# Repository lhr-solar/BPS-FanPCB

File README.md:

# BPS Fan PCB

## Purpose
This board is meant to be a passthrough to control fans from the [BPS Leader Board](https://github.com/lhr-solar/BPS-LeaderPCB). Since it is just digital control, it can also be used to control other digital peripherals, such as contactors, however, it cannot read digital inputs. The traces are sized for 1.5A at 25C increase in temperature.

## Connectors
* One 6 Pin Connector (+12V, GND, 4 Fan Control Pins)
* Twelve 2 Pin Connector (+12V, GND)

## Lights
* One LED that turns on when Power is connected to board

## BOM
https://www.mouser.com/ProjectManager/ProjectDetail.aspx?AccessID=d15e40a820

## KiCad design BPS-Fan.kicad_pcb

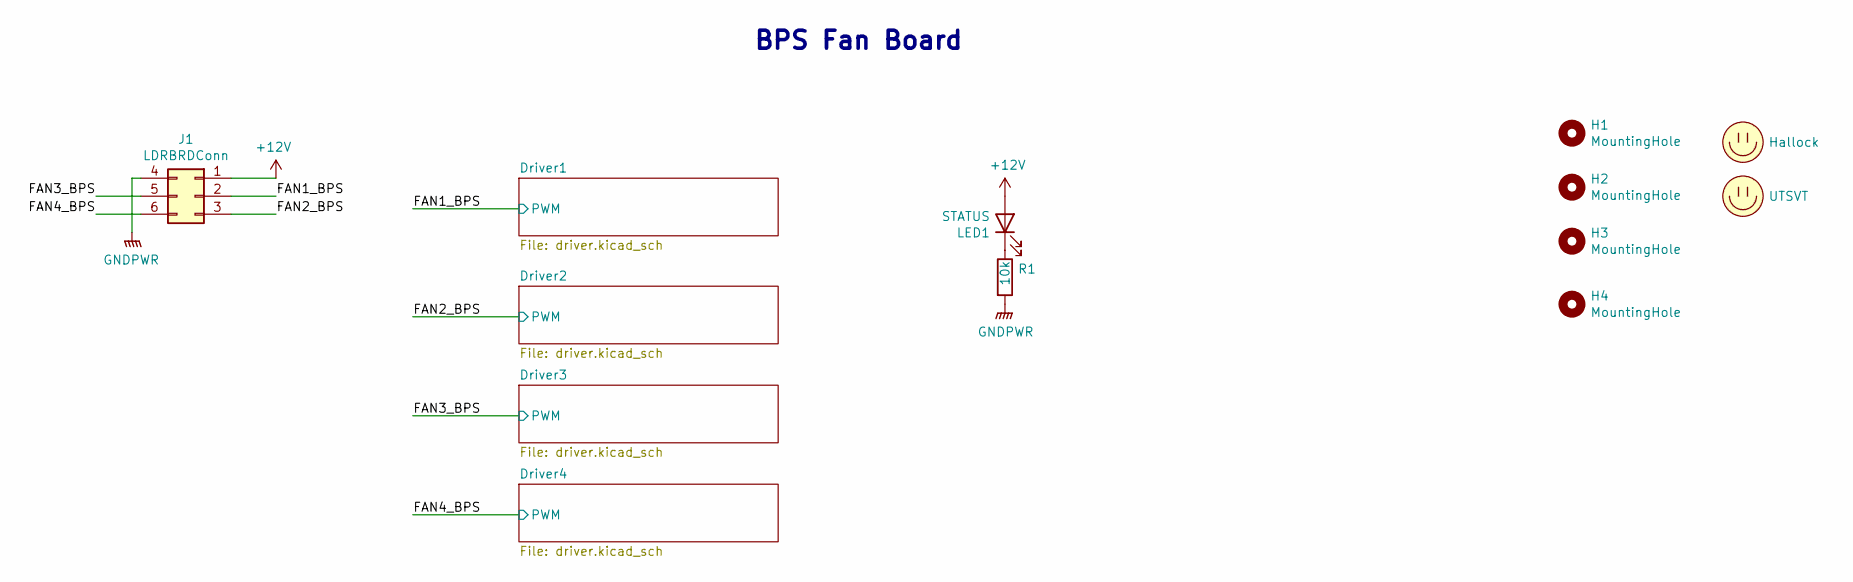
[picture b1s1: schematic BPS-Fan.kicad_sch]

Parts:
H1, H2, H3, H4: MountingHole; MountingHole_3mm
J1: LDRBRDConn; Molex_Micro-Fit_3.0_43045-0612_2x03_P3.00mm_Vertical
LED1: STATUS; LED_0805_2012Metric
LOGO1: Hallock; Hallock_Image_Tiny
LOGO2: UTSVT; UTSVT_Logo_Symbol
R1: 10k; R_0805_2012Metric

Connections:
+12V: J1.1, LED1.2 (A); also elsewhere on the board
/FAN1_BPS: J1.2; also elsewhere on the board
/FAN2_BPS: J1.3; also elsewhere on the board
/FAN3_BPS: J1.5; also elsewhere on the board
/FAN4_BPS: J1.6; also elsewhere on the board
GNDPWR: J1.4, R1.2; also elsewhere on the board
unnamed: LED1.1 (K), R1.1

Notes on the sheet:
BPS Fan Board

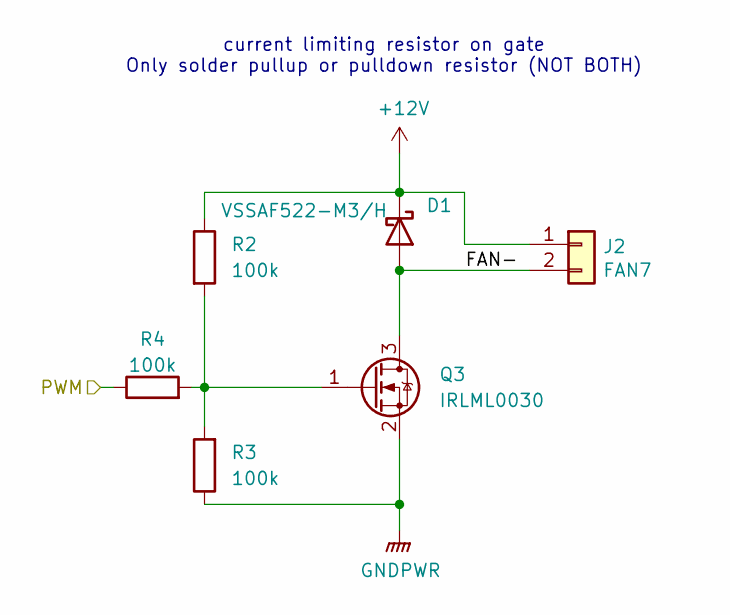
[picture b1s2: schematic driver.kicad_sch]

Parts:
D1: VSSAF522-M3/H; DO-221AC
J2: FAN7; Molex_MicroFit3.0_1x2xP3.00mm_PolarizingPeg_Vertical
Q3: IRLML0030; SOT-23
R2, R3, R4: 100k; R_0805_2012Metric

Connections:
+12V: D1.1 (K), J2.1, R2.1; also elsewhere on the board
/Driver1/FAN-: D1.2 (A), J2.2, Q3.3 (D)
/FAN1_BPS: R4.1; also elsewhere on the board
GNDPWR: Q3.2 (S), R3.1; also elsewhere on the board
unnamed: Q3.1 (G), R2.2, R3.2, R4.2

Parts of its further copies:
D2, D4, D5: VSSAF522-M3/H; DO-221AC
J3, J4, J5: FAN7; Molex_MicroFit3.0_1x2xP3.00mm_PolarizingPeg_Vertical
Q6, Q7, Q8: IRLML0030; SOT-23
R5, R6, R7, R8, R9, R10, R11, R12, R13: 100k; R_0805_2012Metric

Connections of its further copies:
+12V: D2.1 (K), D4.1 (K), D5.1 (K), J3.1, J4.1, J5.1, R5.1, R7.1, R10.1; also elsewhere on the board
/Driver2/FAN-: D2.2 (A), J3.2, Q6.3 (D)
/Driver3/FAN-: D4.2 (A), J4.2, Q7.3 (D)
/Driver4/FAN-: D5.2 (A), J5.2, Q8.3 (D)
/FAN2_BPS: R8.1; also elsewhere on the board
/FAN3_BPS: R12.1; also elsewhere on the board
/FAN4_BPS: R13.1; also elsewhere on the board
GNDPWR: Q6.2 (S), Q7.2 (S), Q8.2 (S), R6.1, R9.1, R11.1; also elsewhere on the board
unnamed: Q6.1 (G), R5.2, R6.2, R8.2
unnamed: Q7.1 (G), R7.2, R9.2, R12.2
unnamed: Q8.1 (G), R10.2, R11.2, R13.2

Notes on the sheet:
current limiting resistor on gate Only solder pullup or pulldown resistor (NOT BOTH)

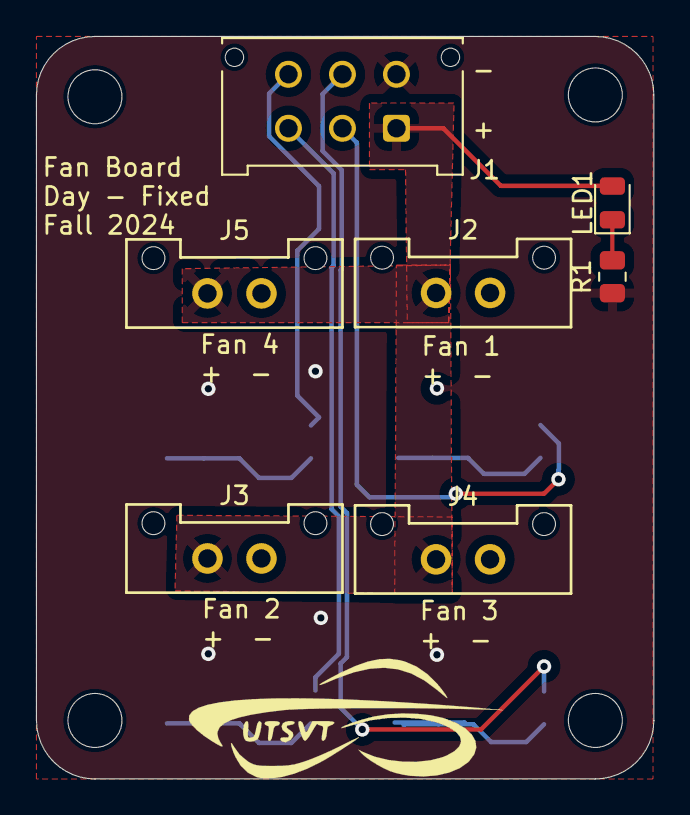
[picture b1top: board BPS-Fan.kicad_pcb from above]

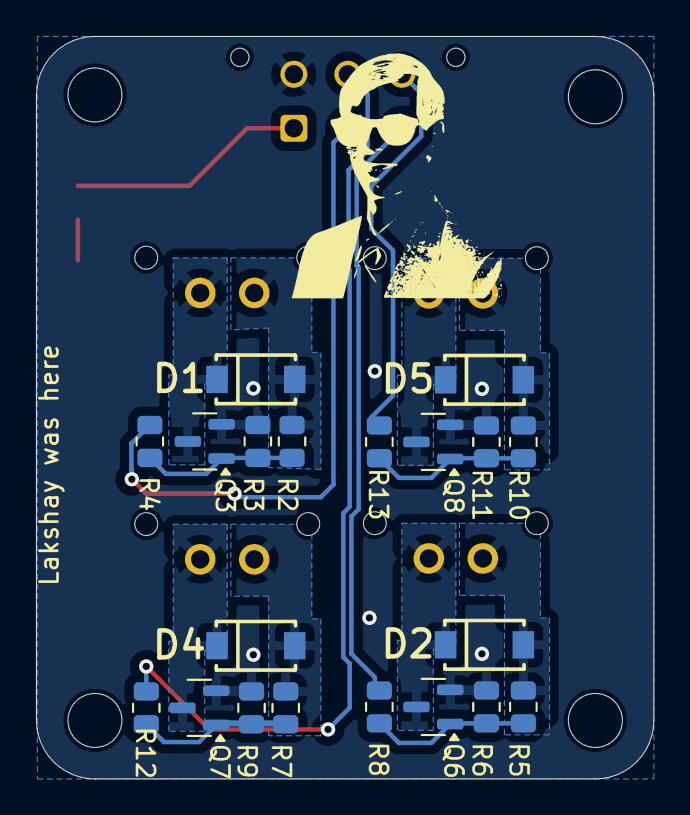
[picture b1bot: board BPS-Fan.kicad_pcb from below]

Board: 2 copper layers, 34.3 x 41.2 mm, 33 parts (21 on the bottom side), 15 nets.

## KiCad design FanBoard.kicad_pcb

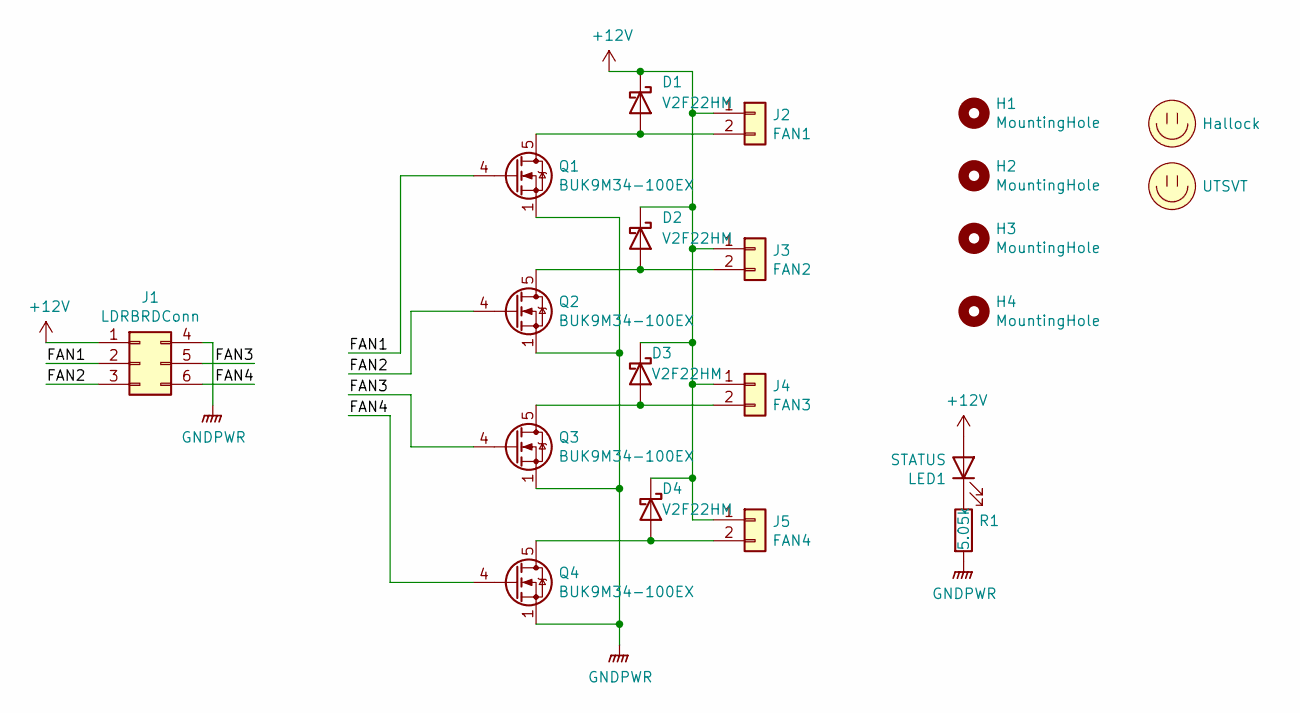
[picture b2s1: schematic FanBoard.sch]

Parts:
D1, D2, D3, D4: V2F22HM
H1, H2, H3, H4: MountingHole; MountingHole_3mm
J1: LDRBRDConn; Molex_Micro-Fit_3.0_43045-0612_2x03_P3.00mm_Vertical
J2: FAN1; Molex_MicroFit3.0_1x2xP3.00mm_PolarizingPeg_Vertical
J3: FAN2; Molex_MicroFit3.0_1x2xP3.00mm_PolarizingPeg_Vertical
J4: FAN3; Molex_MicroFit3.0_1x2xP3.00mm_PolarizingPeg_Vertical
J5: FAN4; Molex_MicroFit3.0_1x2xP3.00mm_PolarizingPeg_Vertical
LED1: STATUS; LED_0805_2012Metric
LOGO1: Hallock; Hallock_Image_Small
LOGO2: UTSVT; UTSVT_Logo_Symbol
Q1, Q2, Q3, Q4: BUK9M34-100EX; LFPAK33
R1: 5.05k; R_0805_2012Metric

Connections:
+12V: D1.1 (K), D2.1 (K), D3.1 (K), D4.1 (K), J1.1, J2.1, J3.1, J4.1, J5.1, LED1.2 (A)
/FAN1: J1.2, Q1.4 (G)
/FAN2: J1.3, Q2.4 (G)
/FAN3: J1.5, Q3.4 (G)
/FAN4: J1.6, Q4.4 (G)
GNDPWR: J1.4, Q1.1 (S), Q1.2 (S), Q1.3 (S), Q2.1 (S), Q2.2 (S), Q2.3 (S), Q3.1 (S), Q3.2 (S), Q3.3 (S), Q4.1 (S), Q4.2 (S), Q4.3 (S), R1.2
unnamed: D1.2 (A), J2.2, Q1.5 (D)
unnamed: D2.2 (A), J3.2, Q2.5 (D)
unnamed: D3.2 (A), J4.2, Q3.5 (D)
unnamed: D4.2 (A), J5.2, Q4.5 (D)
unnamed: LED1.1 (K), R1.1

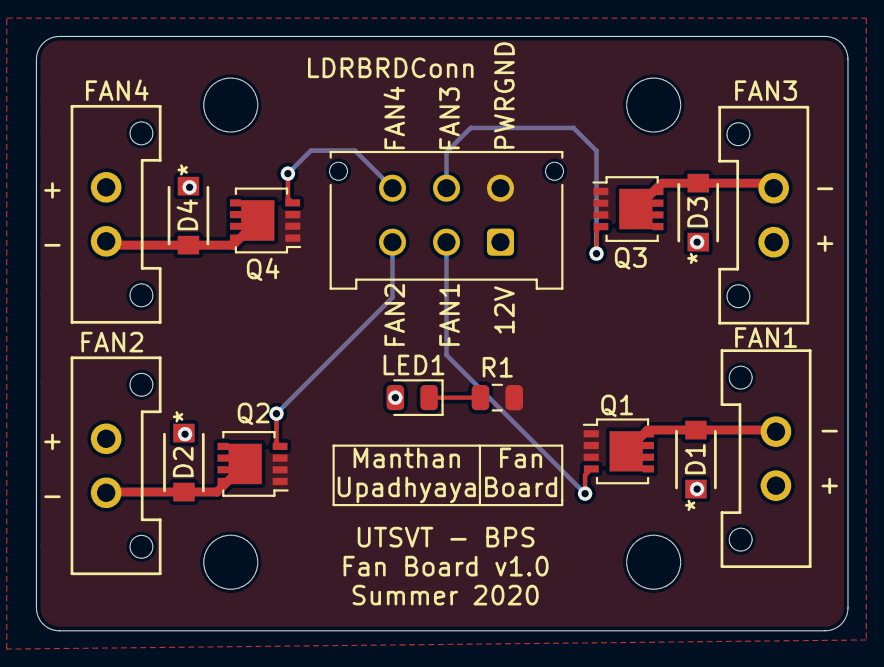
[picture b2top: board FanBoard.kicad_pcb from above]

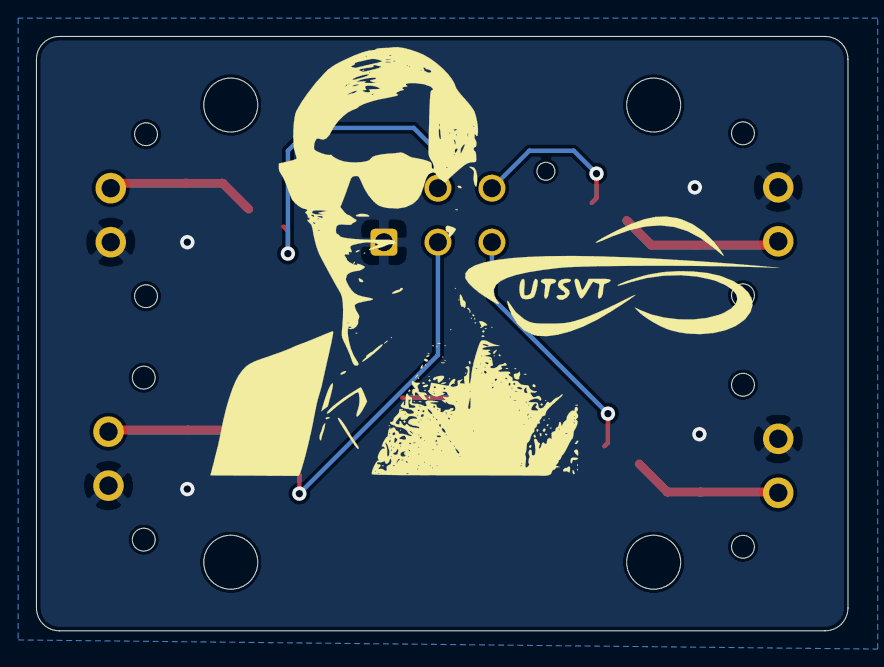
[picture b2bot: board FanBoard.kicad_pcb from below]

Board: 2 copper layers, 45.1 x 33.0 mm, 21 parts (2 on the bottom side), 11 nets.

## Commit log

2020-08-02 Set up for own repository
2020-08-04 Updates reference
2020-08-04 Changed symbol and footprint library paths to include new repositories. Fixed issues with graphic footprints and reference labels
2020-08-06 Makes sure DRC passes. copper plane wasn 't updated
2020-08-08 Fixed resistor value and created Gerber files
2020-08-13 Renames kicad project to match repo
2020-09-01 Renames project to not include PCB
2020-10-03 Adds QuAC
2020-10-17 Adds pdf of schematic and PCB and png of PCB
2022-09-17 Modified BPS fan pcb schematic to support 12 fans instead of 4.
2022-09-24 git@github.com:lhr-solar/BPS-AmperesPCB.git
2022-09-26 reorganizd and fixed labels
2022-10-01 fixed labels, added LED data sheet
2022-10-01 fixed LED data sheet
2022-10-01 fixed bom and added data sheets for connectors
2022-10-22 Replaced mosfet, added Hannah's changes, updated bom and data sheets
2022-10-29 made adjustments after looking at data sheets and realizing we only need 1 mosfet and 1 diode per 3 fans
2022-10-29 made slight adjustment to pass ERC
2022-10-29 cleaned up schematic and fixed shorts
2022-10-29 fixed the last short lol
2022-11-07 Added support for Orion
2022-11-07 Better supports for Orion
2022-11-10 Added PUR
2022-11-19 preliminary idea for layout, NOT cleaned up yet!
2022-11-21 Complete layout of fan board
2022-11-28 fixed user user comments for dimensions
2022-11-30 added space between connectors as suggested by Raymond
2022-12-03 made GNDPWR traces and vias bigger, made drill files and gerber files
2022-12-11 added changes based on Hannah's comments
2022-12-11 added gerber and drill files
2022-12-15 added bom
2023-01-20 Added BOM html
2023-01-21 updated BOM and data sheet in schematic
2023-05-06 Removed zip files and incorporated new submodule
2023-05-06 Updated to KiCAD 7
2023-05-06 Added ReadME Documentation & Version History
2024-09-26 fan go brrr
2024-09-26 ooga booga
2024-09-26 PEDRO SANTACRUZ
2024-09-30 layout go brrr
2024-09-30 skibbidi toilet
2024-10-04 skibbidi fan
2024-10-05 done
2024-10-14 gerbers
2024-11-04 Daybreak rework (#8)
    * fan go brrr
    * ooga booga
    * PEDRO SANTACRUZ
    * layout go brrr
    * skibbidi toilet
    * skibbidi fan

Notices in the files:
parts and their libraries:
Copyright 2016 Accelerated Designs. All rights reserved.
